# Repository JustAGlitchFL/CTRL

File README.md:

# CTRL
A split semi-compact keyboard with extra features

bom and pics soon(tm)

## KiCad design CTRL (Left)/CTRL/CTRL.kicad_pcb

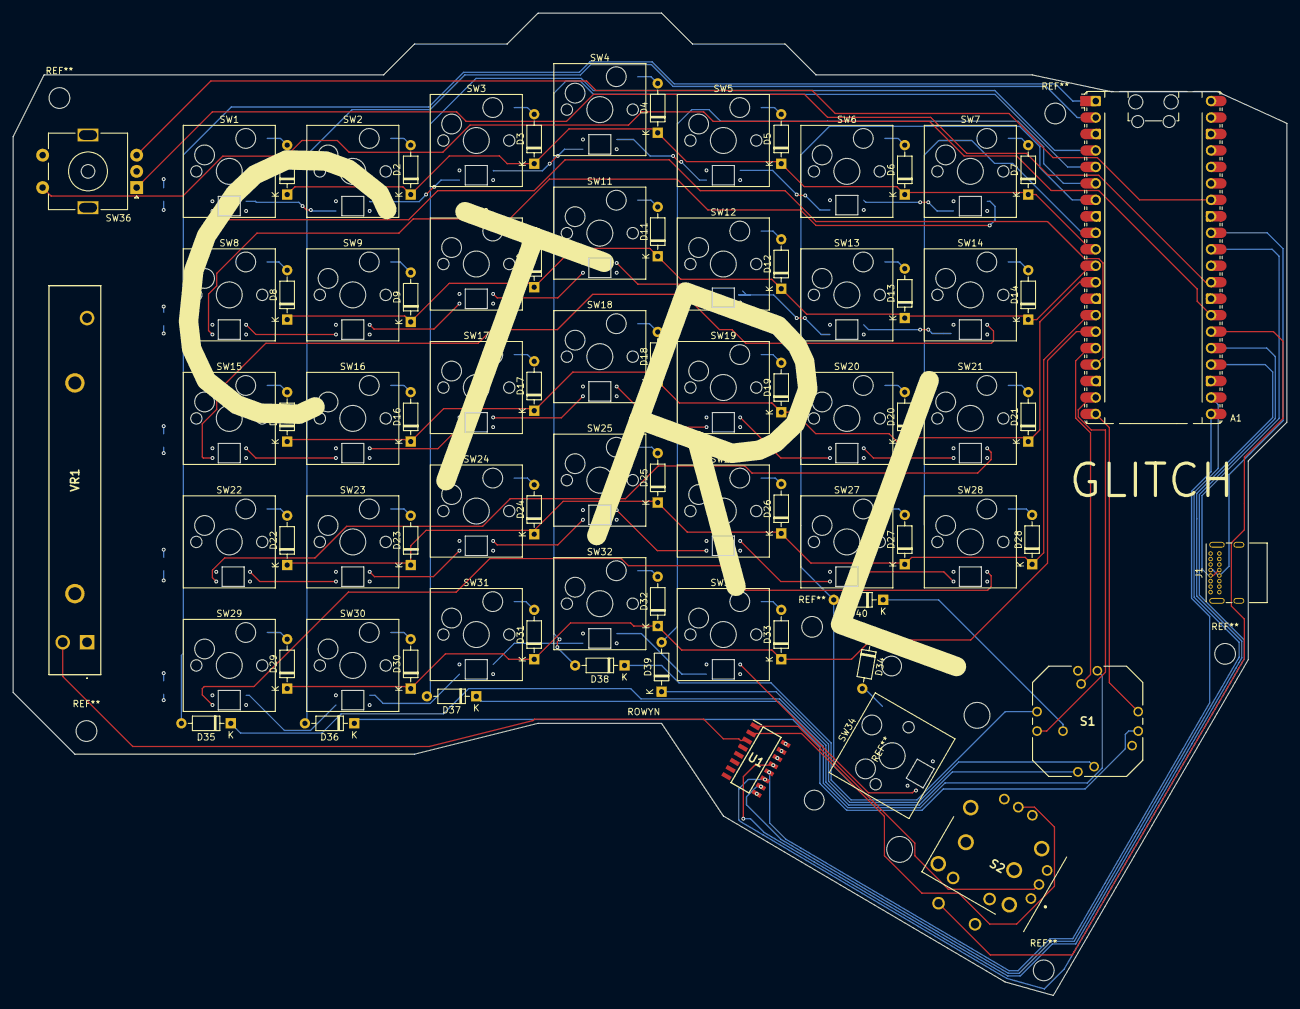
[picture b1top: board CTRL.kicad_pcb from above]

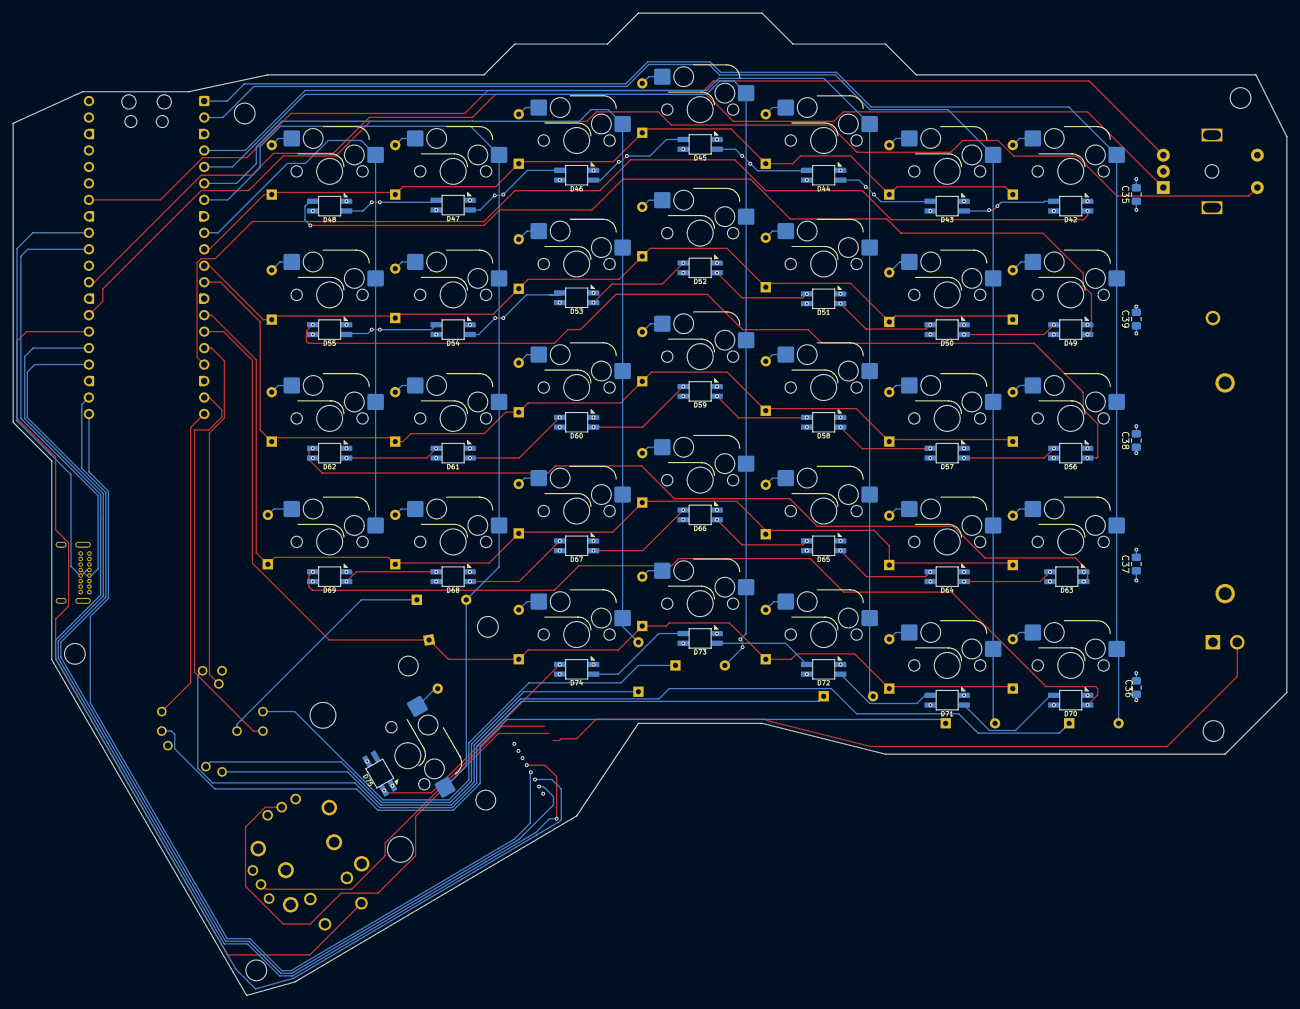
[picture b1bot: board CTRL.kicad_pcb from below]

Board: 4 copper layers, 196.4 x 151.4 mm, 120 parts (39 on the bottom side), 102 nets.

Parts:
A1: RaspberryPi_Pico; RaspberryPi_Pico_Common_Unspecified
C35, C36, C37, C38, C39: C; C_0805_2012Metric_Pad1.18x1.45mm_HandSolder
D1, D2, D3, D4, D5, D6, D7, D8, D9, D10, D11, D12, D13, D14, D15, D16, D17, D18, D19, D20, D21, D22, D23, D24, D25, D26, D27, D28, D29, D30, D31, D32, D33, D34, D35, D36, D37, D38, D39, D40: D; D_DO-35_SOD27_P7.62mm_Horizontal
D42, D43, D44, D45, D46, D47, D48, D49, D50, D51, D52, D53, D54, D55, D56, D57, D58, D59, D60, D61, D62, D63, D64, D65, D66, D67, D68, D69, D70, D71, D72, D73, D74, D75: SK6812MINI; SK6812MINI-E
J1: USB_C_Receptacle_USB2.0_14P; USB_C_Receptacle_GCT_USB4085
S1: RKJXT1F42001
S2: RKJXV122400R
SW1, SW2, SW3, SW4, SW5, SW6, SW7, SW8, SW9, SW10, SW11, SW12, SW13, SW14, SW15, SW16, SW17, SW18, SW19, SW20, SW21, SW22, SW23, SW24, SW25, SW26, SW27, SW28, SW29, SW30, SW31, SW32, SW33: SW_Push; Hotswap_MX_1.00u
SW34: SPACE; Hotswap_MX_2.00u
SW36: RotaryEncoder_Switch; RotaryEncoder_Alps_EC11E-Switch_Vertical_H20mm_MountingHoles
U1: MCP3008; SOIC127P600X175-16N
VR1: RS45111A900F

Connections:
+3V3: A1.36 (3V3), A1.39 (VSYS)
+5V: A1.40 (VBUS), C35.1, C36.1, C37.1, C38.1, C39.1, D42.4 (VDD), D43.4 (VDD), D44.4 (VDD), D45.4 (VDD), D46.4 (VDD), D47.4 (VDD), D48.4 (VDD), D49.4 (VDD), D50.4 (VDD), D51.4 (VDD), D52.4 (VDD), D53.4 (VDD), D54.4 (VDD), D55.4 (VDD), D56.4 (VDD), D57.4 (VDD), D58.4 (VDD), D59.4 (VDD), D60.4 (VDD), D61.4 (VDD), D62.4 (VDD), D63.4 (VDD), D64.4 (VDD), D65.4 (VDD), D66.4 (VDD), D67.4 (VDD), D68.4 (VDD), D69.4 (VDD), D70.4 (VDD), D71.4 (VDD), D72.4 (VDD), D73.4 (VDD), D74.4 (VDD), D75.4 (VDD), J1.A4 (VBUS), J1.A9 (VBUS), J1.B4 (VBUS), J1.B9 (VBUS), S2.A11, S2.B11, U1.15 (Vref), U1.16 (Vdd), VR1.1 (CCW)
COL0: A1.1 (GPIO0), D35.2 (A), SW1.1, SW8.1, SW15.1, SW22.1, SW29.1
COL1: A1.2 (GPIO1), D36.2 (A), SW2.1, SW9.1, SW16.1, SW23.1, SW30.1
COL2: A1.4 (GPIO2), D37.2 (A), SW3.1, SW10.1, SW17.1, SW24.1, SW31.1
COL3: A1.5 (GPIO3), D38.2 (A), SW4.1, SW11.1, SW18.1, SW25.1, SW32.1
COL4: A1.6 (GPIO4), D39.2 (A), SW5.1, SW12.1, SW19.1, SW26.1, SW33.1
COL5: A1.7 (GPIO5), D40.2 (A), SW6.1, SW13.1, SW20.1, SW27.1, SW34.1
COL6: A1.9 (GPIO6), SW7.1, SW14.1, SW21.1, SW28.1
EC1A: A1.19 (GPIO14), S1.10 (ENCODER_A)
EC1B: A1.20 (GPIO15), S1.5 (ENCODER_B)
EC2A: A1.29 (GPIO22), SW36.A
EC2B: A1.34 (GPIO28_ADC2), SW36.B
ECROW: A1.16 (GPIO12), S1.7 (COM)
GND: A1.3 (GND), A1.8 (GND), A1.13 (GND), A1.18 (GND), A1.23 (GND), A1.28 (GND), A1.38 (GND), C35.2, C36.2, C37.2, C38.2, C39.2, D42.2 (VSS), D43.2 (VSS), D44.2 (VSS), D45.2 (VSS), D46.2 (VSS), D47.2 (VSS), D48.2 (VSS), D49.2 (VSS), D50.2 (VSS), D51.2 (VSS), D52.2 (VSS), D53.2 (VSS), D54.2 (VSS), D55.2 (VSS), D56.2 (VSS), D57.2 (VSS), D58.2 (VSS), D59.2 (VSS), D60.2 (VSS), D61.2 (VSS), D62.2 (VSS), D63.2 (VSS), D64.2 (VSS), D65.2 (VSS), D66.2 (VSS), D67.2 (VSS), D68.2 (VSS), D69.2 (VSS), D70.2 (VSS), D71.2 (VSS), D72.2 (VSS), D73.2 (VSS), D74.2 (VSS), D75.2 (VSS), J1.A1 (GND), J1.A12 (GND), J1.B1 (GND), J1.B12 (GND), J1.S1 (SHIELD), S1.3 (GND_TERMINAL), S1.8 (ENCODER_COM), S2.A13, S2.B13, S2.C1, SW36.C, SW36.S1, U1.9 (DGND), U1.14 (AGND), VR1.3 (CW)
unnamed: A1.21 (GPIO16), U1.12 (Dout)
unnamed: A1.22 (GPIO17), U1.10 (~CS/SHDN)
unnamed: A1.24 (GPIO18), U1.13 (CLK)
unnamed: A1.25 (GPIO19), U1.11 (Din)
unnamed: A1.31 (GPIO26_ADC0), J1.A6 (D+), J1.B6 (D+)
unnamed: A1.32 (GPIO27_ADC1), J1.A7 (D-), J1.B7 (D-)
unnamed: D1.2 (A), SW1.2
unnamed: D2.2 (A), SW2.2
unnamed: D3.2 (A), SW3.2
unnamed: D4.2 (A), SW4.2
unnamed: D5.2 (A), SW5.2
unnamed: D6.2 (A), SW6.2
unnamed: D7.2 (A), SW7.2
unnamed: D8.2 (A), SW8.2
unnamed: D9.2 (A), SW9.2
unnamed: D10.2 (A), SW10.2
unnamed: D11.2 (A), SW11.2
unnamed: D12.2 (A), SW12.2
unnamed: D13.2 (A), SW13.2
unnamed: D14.2 (A), SW14.2
unnamed: D15.2 (A), SW15.2
unnamed: D16.2 (A), SW16.2
unnamed: D17.2 (A), SW17.2
unnamed: D18.2 (A), SW18.2
unnamed: D19.2 (A), SW19.2
unnamed: D20.2 (A), SW20.2
unnamed: D21.2 (A), SW21.2
unnamed: D22.2 (A), SW22.2
unnamed: D23.2 (A), SW23.2
unnamed: D24.2 (A), SW24.2
unnamed: D25.2 (A), SW25.2
unnamed: D26.2 (A), SW26.2
unnamed: D27.2 (A), SW27.2
unnamed: D28.2 (A), SW28.2
unnamed: D29.2 (A), SW29.2
unnamed: D30.2 (A), SW30.2
unnamed: D31.2 (A), SW31.2
unnamed: D32.2 (A), SW32.2
unnamed: D33.2 (A), SW33.2
unnamed: D34.2 (A), SW34.2
unnamed: D35.1 (K), S1.1 (A)
unnamed: D36.1 (K), S1.4 (B)
unnamed: D37.1 (K), S1.6 (C)
unnamed: D38.1 (K), S1.9 (D_1)
unnamed: D39.1 (K), S1.2 (PUSH)
unnamed: D40.1 (K), S1.11 (D_2)
unnamed: D42.1 (DOUT), D43.3 (DIN)
unnamed: D43.1 (DOUT), D44.3 (DIN)
unnamed: D44.1 (DOUT), D45.3 (DIN)
unnamed: D45.1 (DOUT), D46.3 (DIN)
unnamed: D46.1 (DOUT), D47.3 (DIN)
unnamed: D47.1 (DOUT), D48.3 (DIN)
unnamed: D48.1 (DOUT), D49.3 (DIN)
unnamed: D49.1 (DOUT), D50.3 (DIN)
unnamed: D50.1 (DOUT), D51.3 (DIN)
unnamed: D51.1 (DOUT), D52.3 (DIN)
unnamed: D52.1 (DOUT), D53.3 (DIN)
unnamed: D55.1 (DOUT), D56.3 (DIN)
unnamed: D56.1 (DOUT), D57.3 (DIN)
unnamed: D57.1 (DOUT), D58.3 (DIN)
unnamed: D58.1 (DOUT), D59.3 (DIN)
unnamed: D59.1 (DOUT), D60.3 (DIN)
unnamed: D60.1 (DOUT), D61.3 (DIN)
unnamed: D61.1 (DOUT), D62.3 (DIN)
unnamed: D62.1 (DOUT), D63.3 (DIN)
unnamed: D63.1 (DOUT), D64.3 (DIN)
unnamed: D64.1 (DOUT), D65.3 (DIN)
unnamed: D65.1 (DOUT), D66.3 (DIN)
unnamed: D66.1 (DOUT), D67.3 (DIN)
unnamed: D67.1 (DOUT), D68.3 (DIN)
unnamed: D68.1 (DOUT), D69.3 (DIN)
unnamed: D69.1 (DOUT), D70.3 (DIN)
unnamed: D70.1 (DOUT), D71.3 (DIN)
unnamed: D71.1 (DOUT), D72.3 (DIN)
unnamed: D72.1 (DOUT), D73.3 (DIN)
unnamed: D73.1 (DOUT), D74.3 (DIN)
unnamed: S2.A12, U1.1 (CH0)
unnamed: S2.B12, U1.2 (CH1)
unnamed: U1.3 (CH2), VR1.2 (WIPER)
Push1: A1.26 (GPIO20), S2.B1
Push2: A1.27 (GPIO21), SW36.S2
RGB: A1.17 (GPIO13), D42.3 (DIN)
ROW0: A1.10 (GPIO7), D1.1 (K), D2.1 (K), D3.1 (K), D4.1 (K), D5.1 (K), D6.1 (K), D7.1 (K)
ROW1: A1.11 (GPIO8), D8.1 (K), D9.1 (K), D10.1 (K), D11.1 (K), D12.1 (K), D13.1 (K), D14.1 (K)
ROW2: A1.12 (GPIO9), D15.1 (K), D16.1 (K), D17.1 (K), D18.1 (K), D19.1 (K), D20.1 (K), D21.1 (K)
ROW3: A1.14 (GPIO10), D22.1 (K), D23.1 (K), D24.1 (K), D25.1 (K), D26.1 (K), D27.1 (K), D28.1 (K)
ROW4: A1.15 (GPIO11), D29.1 (K), D30.1 (K), D31.1 (K), D32.1 (K), D33.1 (K), D34.1 (K)

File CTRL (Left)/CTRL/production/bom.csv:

Designator,Footprint,Quantity,Value,LCSC Part #
A1,RaspberryPi_Pico_Common_Unspecified,1,RaspberryPi_Pico,
"C35, C36, C37, C38, C39",0805,5,C,
"D1, D10, D11, D12, D13, D14, D15, D16, D17, D18, D19, D2, D20, D21, D22, D23, D24, D25, D26, D27, D28, D29, D3, D30, D31, D32, D33, D34, D35, D36, D37, D38, D39, D4, D40, D5, D6, D7, D8, D9",D_DO-35_SOD27_P7.62mm_Horizontal,40,D,
"D42, D43, D44, D45, D46, D47, D48, D49, D50, D51, D52, D53, D54, D55, D56, D57, D58, D59, D60, D61, D62, D63, D64, D65, D66, D67, D68, D69, D70, D71, D72, D73, D74, D75",SK6812MINI-E,34,SK6812MINI,
J1,USB_C_Receptacle_GCT_USB4085,1,USB_C_Receptacle_USB2.0_14P,
S1,RKJXT1F42001,1,RKJXT1F42001,
S2,RKJXV122400R,1,RKJXV122400R,
"SW1, SW10, SW11, SW12, SW13, SW14, SW15, SW16, SW17, SW18, SW19, SW2, SW20, SW21, SW22, SW23, SW24, SW25, SW26, SW27, SW28, SW29, SW3, SW30, SW31, SW32, SW33, SW4, SW5, SW6, SW7, SW8, SW9",Hotswap_MX_1.00u,33,SW_Push,
SW34,Hotswap_MX_2.00u,1,SPACE,
SW36,RotaryEncoder_Alps_EC11E-Switch_Vertical_H20mm_MountingHoles,1,RotaryEncoder_Switch,
U1,SOIC127P600X175-16N,1,MCP3008,
VR1,RS45111A900F,1,RS45111A900F,

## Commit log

2025-05-31 kicad stuff
2025-07-08 sync
